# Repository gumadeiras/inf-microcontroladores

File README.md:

# Microcontroladores
Gustavo, Lúcio e Rodrigo

[Criando Usuário](https://github.com/gumadeiras/inf-microcontroladores/blob/master/begin.sh)

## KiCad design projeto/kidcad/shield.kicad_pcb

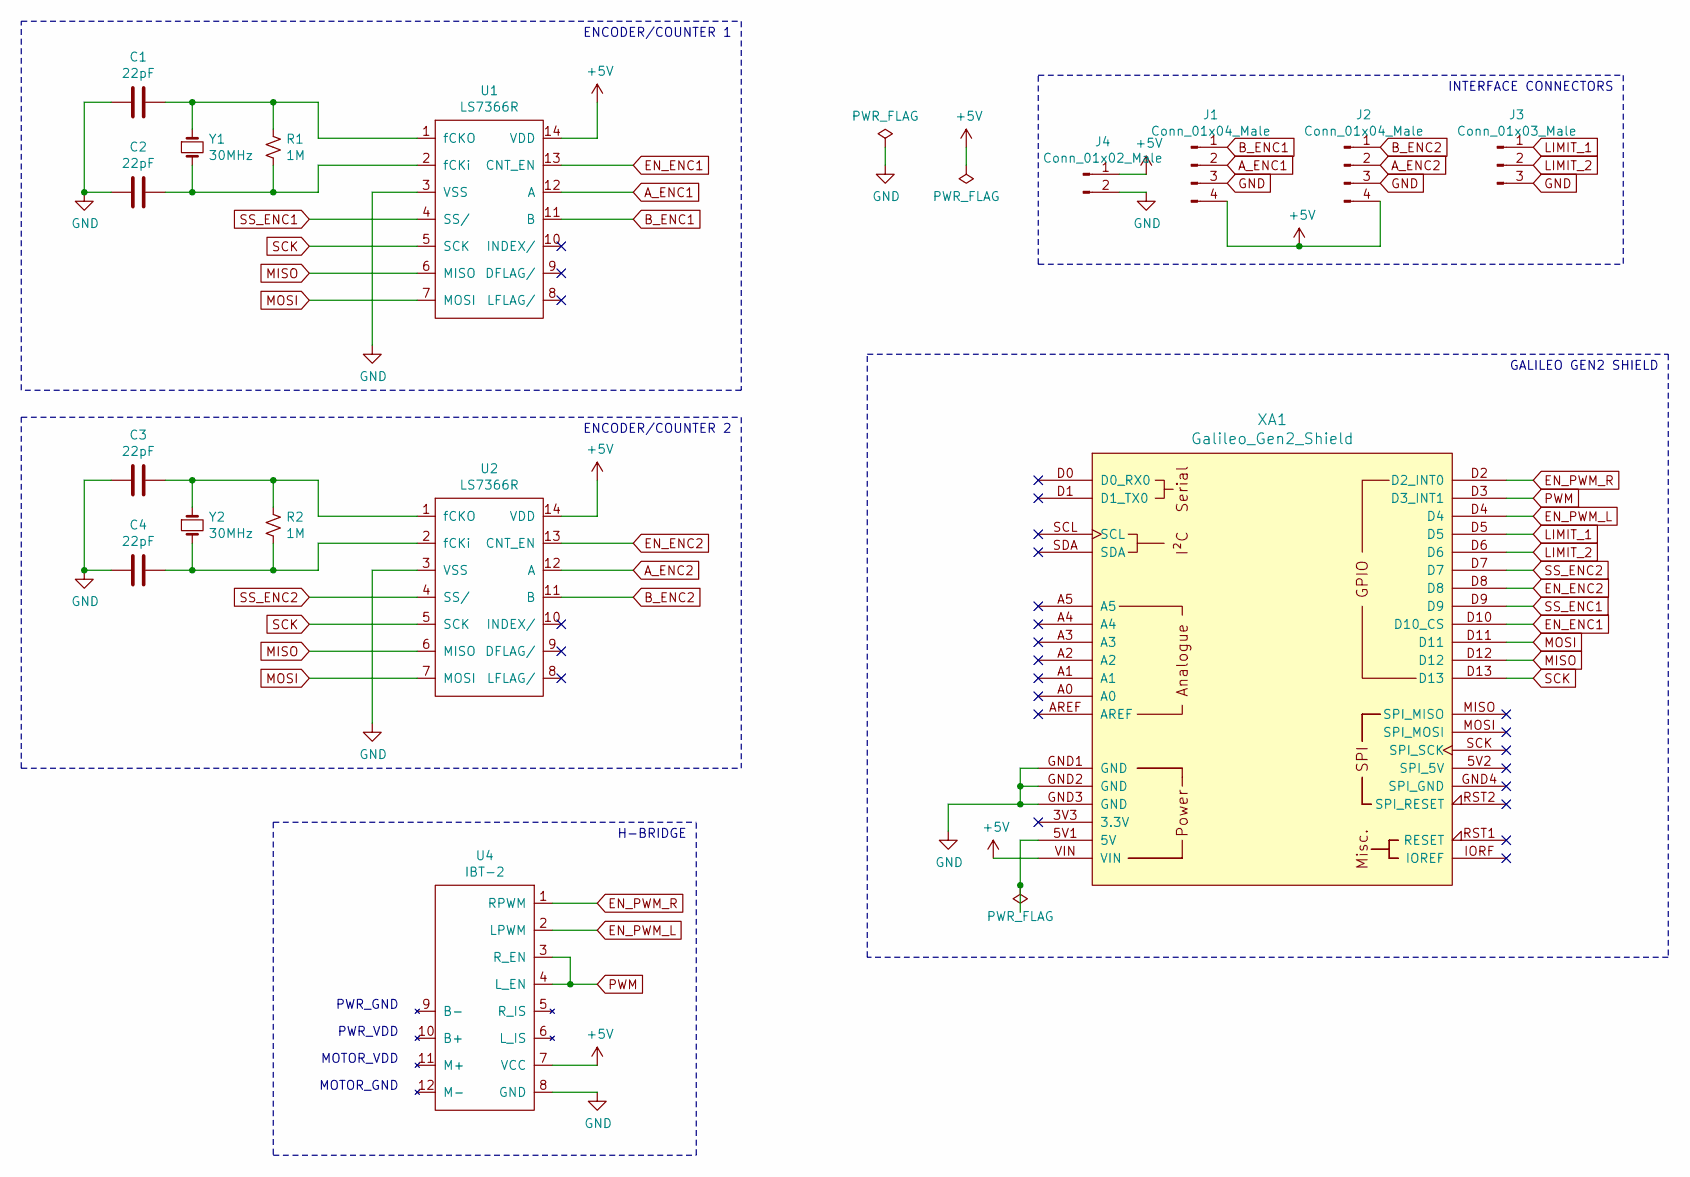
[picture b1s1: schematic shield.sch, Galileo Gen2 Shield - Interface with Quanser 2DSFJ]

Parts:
C1, C2, C3, C4: 22pF; C_Disc_D3.8mm_W2.6mm_P2.50mm
J1, J2: Conn_01x04_Male; PinHeader_1x04_P2.54mm_Vertical
J3: Conn_01x03_Male; PinHeader_1x03_P2.54mm_Vertical
J4: Conn_01x02_Male; PinHeader_1x02_P2.54mm_Vertical
R1, R2: 1M; R_Axial_DIN0204_L3.6mm_D1.6mm_P7.62mm_Horizontal
U1, U2: LS7366R; DIP-14_W7.62mm
U4: IBT-2; PinSocket_2x04_P2.54mm_Horizontal
XA1: Galileo_Gen2_Shield; Arduino_Uno_Shield
Y1, Y2: 30MHz; Crystal_HC49-U_Vertical

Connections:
+5V: J1.4, J2.4, J4.1, U1.14 (VDD), U2.14 (VDD), U4.7 (VCC), XA1.VIN
A_ENC1: J1.2, U1.12 (A)
A_ENC2: J2.2, U2.12 (A)
B_ENC1: J1.1, U1.11 (B)
B_ENC2: J2.1, U2.11 (B)
EN_ENC1: U1.13 (CNT_EN), XA1.D10 (D10_CS)
EN_ENC2: U2.13 (CNT_EN), XA1.D8
EN_PWM_L: U4.2 (LPWM), XA1.D4
EN_PWM_R: U4.1 (RPWM), XA1.D2 (D2_INT0)
GND: C1.2, C2.1, C3.2, C4.1, J1.3, J2.3, J3.3, J4.2, U1.3 (VSS), U2.3 (VSS), U4.8 (GND), XA1.GND1 (GND), XA1.GND2 (GND), XA1.GND3 (GND)
LIMIT_1: J3.1, XA1.D5
LIMIT_2: J3.2, XA1.D6
MISO: U1.6 (MISO), U2.6 (MISO), XA1.D12
MOSI: U1.7 (MOSI), U2.7 (MOSI), XA1.D11
unnamed: C1.1, R1.1, U1.1 (fCKO), Y1.1
unnamed: C2.2, R1.2, U1.2 (fCKi), Y1.2
unnamed: C3.1, R2.1, U2.1 (fCKO), Y2.1
unnamed: C4.2, R2.2, U2.2 (fCKi), Y2.2
PWM: U4.3 (R_EN), U4.4 (L_EN), XA1.D3 (D3_INT1)
SCK: U1.5 (SCK), U2.5 (SCK), XA1.D13
SS_ENC1: U1.4 (SS/), XA1.D9
SS_ENC2: U2.4 (SS/), XA1.D7

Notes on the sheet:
MOTOR_GND
MOTOR_VDD
PWR_VDD
PWR_GND
GALILEO GEN2 SHIELD
INTERFACE CONNECTORS
ENCODER/COUNTER 1
ENCODER/COUNTER 2
H-BRIDGE

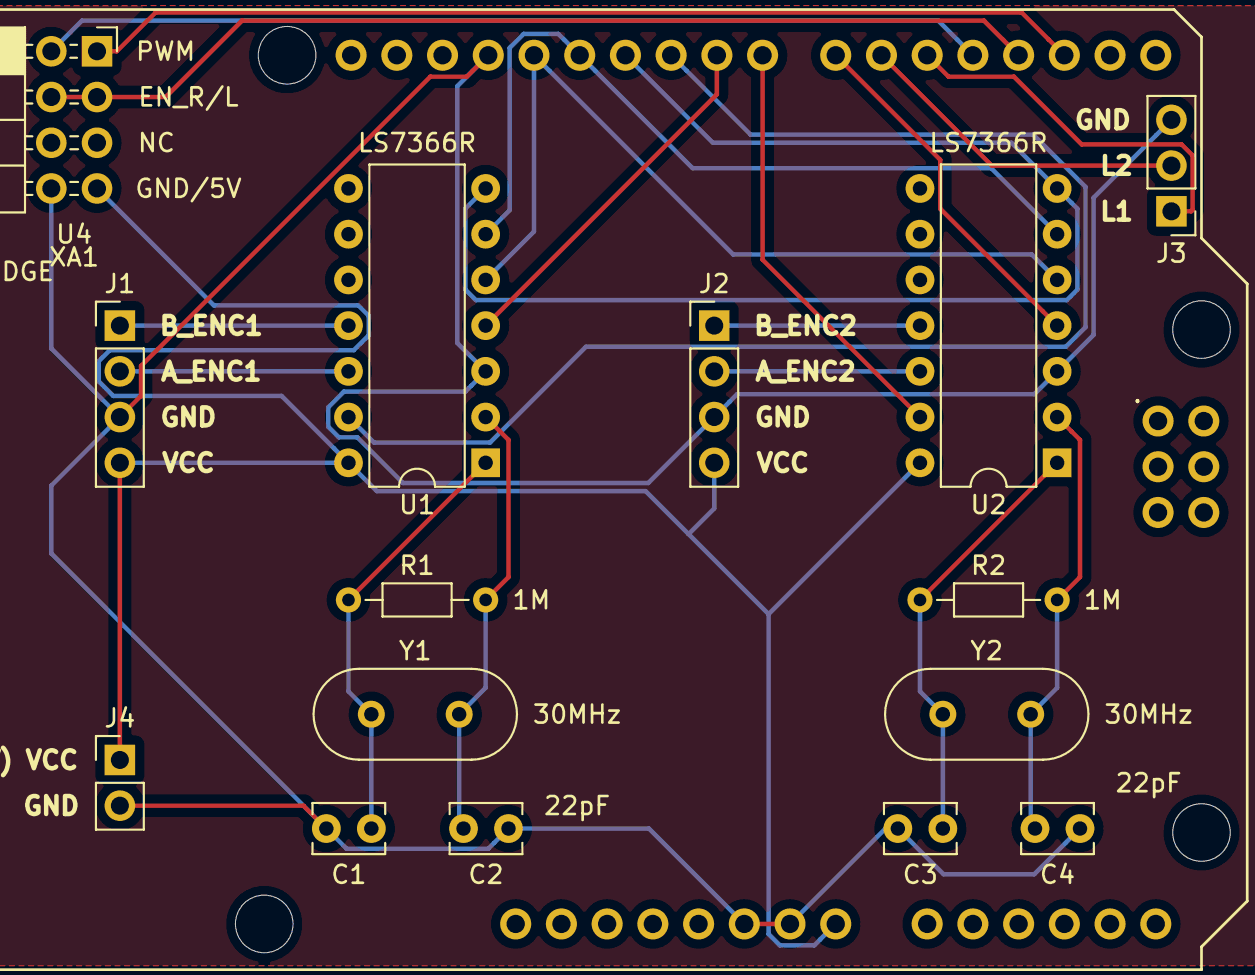
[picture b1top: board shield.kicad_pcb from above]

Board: 2 copper layers, 16 parts (0 on the bottom side), 22 nets.

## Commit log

2019-09-28 first
2019-09-28 second
2019-09-28 README criando user
2019-09-28 labs galileo bin
2019-09-28 lab5
2019-09-28 lab05
2019-09-28 lab06
2019-09-29 Tutorial ssh
2019-09-30 assets
2019-09-30 tutorial indice
2019-10-02 bins
2019-10-03 lab07
2019-10-16 Includes lab08
2019-10-17 added pdfs
2019-10-18 galileo shield
2019-10-18 added connectors
2019-10-18 updated 4pin headers
2019-10-18 updated design
2019-10-18 added space on board
2019-10-18 final schematic
2019-10-19 added init script for H-Bridge pins
2019-10-19 correct pins init.d
2019-10-19 encoder header
2019-10-19 main will have API demonstration
2019-10-19 motor driver in C (not tested)
2019-10-19 pwm works :)
2019-10-19 pwm lib (set by percentage or voltage; not tested)
2019-10-19 updated header files
2019-10-20 changed pins to match working pwm
2019-10-21 updated gerber files
2019-10-26 dump
2019-11-10 counter galileo
2019-11-23 partial script for quanser demo
2019-11-23 partial PID test
2019-11-24 first PID for testing
2019-11-24 pid compiles
2019-11-24 fixed pid bug
2019-11-24 bug fixes, added pid consts as parameters from cli
2019-11-26 changed pins for h-bridge
2019-11-29 added doxygen docs
2019-11-29 updated doxygen
2019-11-29 updated docs
2019-11-29 fixed compiler warnings
2019-11-29 added shield files for corrosion
2019-11-29 colocando o nome dos VACILÃO
2019-12-02 added recent labs
